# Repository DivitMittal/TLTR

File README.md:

<h1 align='center'>TLTR</h1>
<div align='center'>
    
</div>

---

<div align='center'>

</div>

---

A bespoke cross-platform multi-layer 38-key keyboard layout for programmers, i.e., it optimizes for:

1. Minimal mouse/trackpad dependency
2. Convenient numbers & symbols access
3. Execution of complex keyboard shortcuts w/o cumbersome finger gymnastics.
4. Interoperability b/w [ANSI US](https://commons.wikimedia.org/wiki/File:ANSI_Keyboard_Layout_Diagram_with_Form_Factor.svg) & other ergo-split keyboard configurations, viz., [corne](https://github.com/foostan/crkbd/), [cantor](https://github.com/diepala/cantor), [ferris](https://github.com/pierrechevalier83/ferris), etc..

---

| Layers                                                                                        | Functionality                  |
| --------------------------------------------------------------------------------------------- | ------------------------------ |
| [Colemak Mod-DH(Curl), Wide, Angle](https://github.com/ColemakMods/mod-dh?tab=readme-ov-file) | English                        |
| TL                                                                                            | Navigation & Modifiers keys    |
| TR                                                                                            | Numbers & Symbols              |
| TLTR                                                                                          | Mouse, Media & Display control |

<div align='center'>
    <table>
        <tr>
            <th>Split Keyboard Layout</th>
            <th>ANSI Keyboard Layout</th>
        </tr>
        <tr>
            <td>
                
            </td>
            <td>
                
            </td>
        </tr>
    </table>
</div>

---

## Can be deployed via:

### Software-based (works with any keyboard):

1. [Kanata](https://github.com/jtroo/kanata/) - Cross-platform key remapper
   1. macOS
      - Dependencies:
        1. [Karabiner-DriverKit](https://github.com/pqrs-org/Karabiner-DriverKit-VirtualHIDDevice)
   2. Windows
      - Dependencies:
        1. [InterceptionDriver](https://github.com/oblitum/Interception)
   3. \*nix
      - Dependencies:
        1. `xset` (X11) for the display-off key

### Hardware-based (firmware flashed to keyboard):

2. [QMK Firmware](https://qmk.fm/) - For programmable keyboards
   - Target keyboard: [Piantor](https://github.com/beekeeb/piantor) (RP2040-based Cantor variant)
   - Firmware location: `qmk/piantor_tltr/`
   - Build instructions: See [qmk/README.md](qmk/README.md)

---

## Physical implementation

### Column-staggered ergo-split keyboard, i.e., [Cantor](https://github.com/diepala/cantor)([Piantor](https://github.com/beekeeb/piantor) specifically) with Cherry MX1A Red Switches

---

## Optional: Dual Foot Pedals

Hands-free control via USB or serial foot pedals. Includes both Arduino Uno (serial) and RP2040 (native USB HID) sketches with gesture recognition.

See [pedals/README.md](./pedals/) for setup, keymap, and configuration.

The RP2040 pedal sketch has a matching carrier PCB and 3D-printable enclosure. Both are generated: the board as a KiCad 10 project, the enclosure with build123d. See [hardware/README.md](./hardware/).

---

**Inspired by:** [Seniply](https://github.com/stevep99/seniply)

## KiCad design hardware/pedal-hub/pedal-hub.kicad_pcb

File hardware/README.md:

# Hardware

Electronics (KiCad 10) and 3D-printable enclosures (build123d) for TLTR
accessories. Every KiCad file here is **generated**: edit the generator, then
regenerate. The committed `.kicad_*` files are what you open in KiCad, send to
a fab, or inspect with the Konnect MCP.

| Board | What | Firmware |
| --- | --- | --- |
| [`pedal-hub/`](pedal-hub/) | RP2040-Zero carrier with two 6.35 mm footswitch jacks | [`pedals/rp2040-dual-pedal-hid`](../pedals/rp2040-dual-pedal-hid/) |

## Layout

```
hardware/
  kigen/               generator library: S-expression I/O, schematic writer, pcbnew board builder
  <board>/generate.py  the design: parts, nets, placement, routing, enclosure data
  <board>/*.kicad_*    generated KiCad 10 project (schematic, board, project-local libraries)
  <board>/docs/        schematic PDF/SVG, top/bottom copper renders
  <board>/<board>.step bare-board STEP from KiCad
  <board>/mechanical.json  outline, holes, edge cutouts, heights -> cad/enclosure.py
cad/
  enclosure.py         parametric tray + lid (build123d)
  out/<board>/         tray/lid STEP + STL, fit-check assembly STEP, preview SVG
scripts/
  kicad                run kicad-cli / KiCad's python3: native install, else the kicad/kicad:10.0 container
  hardware             regenerate everything (boards, checks, exports, enclosures)
```

## Regenerate

```sh
scripts/hardware                                   # all boards + enclosures
scripts/kicad python3 hardware/pedal-hub/generate.py --export   # one board
uv run cad/enclosure.py hardware/pedal-hub/mechanical.json      # one enclosure
```

`generate.py` fails unless all of these are clean:

- `kicad-cli sch erc` (all severities)
- `kicad-cli pcb drc --schematic-parity` (all severities, including unconnected items)

Reports go to `.validation/<board>/` (gitignored). The
[`hardware-check`](../.github/workflows/hardware-check.yml) workflow runs the
same generators in the `kicad/kicad:10.0` container and fails if the committed
KiCad files drift from their generators.

**Requirements:** a native KiCad 10, or Docker for the container fallback. On
macOS nixpkgs marks KiCad broken, so install KiCad.app or run a Docker VM, such
as `colima start`. Enclosures need [uv](https://docs.astral.sh/uv/). It
installs `build123d` from the script's inline metadata.

## Why generated KiCad, not atopile

atopile 0.15 announces itself as the last CLI release. Its successor is a
hosted app that needs `ato auth login`. Plain KiCad files plus a small
deterministic generator keep the design reviewable in git, buildable offline
and in CI, and openable in the KiCad GUI and in [Konnect](https://github.com/mixelpixx/Konnect)
for hand edits. If you hand-edit a board in KiCad, port the change back into
`generate.py`, or stop regenerating that board.

## Pedal hub

- **U1** Waveshare RP2040-Zero on pin headers. Only the two side rows are used
  (rows 15.24 mm apart, 2.54 mm pitch). USB-C is flush with the back edge.
- **J1/J2** Neutrik NMJ6HCD2 6.35 mm (¼″) stereo jacks. Tip goes to the GPIO.
  Ring and sleeve go to GND, so TS footswitches and tip-to-ring TRS pedals both
  work.
- **R1/R2 330 Ω + C1/C2 100 nF** series RC on each input. It limits ESD/RF
  pickup on long pedal cables. τ = 33 µs, invisible to the 25 ms firmware
  debounce.
- 2-layer, all through-hole. Signals are on B.Cu; F.Cu is an unbroken ground
  plane. Four M3 holes are 4 mm from the corners.

**BOM:** 1× RP2040-Zero, 2× 1×9 2.54 mm male headers, 2× NMJ6HCD2, 2× 330 Ω
¼ W, 2× 100 nF disc ceramic. Enclosure: 4× M3×20 cap screws, 4× M3 heat-set
inserts (4.0 mm hole), and optionally 4× 10 mm rubber feet.

### Verify before you order

Not all of these come from measurements:

| Item | Source | Status |
| --- | --- | --- |
| RP2040-Zero row spacing 15.24 mm, pin order | community footprint (CountParadox/RP2040-Zero-Kicad) cross-checked with Waveshare pinout | verify with calipers |
| NMJ6HCD2 mouth on the footprint's +X side | stock KiCad footprint, ferrule outline | check datasheet |
| Jack axis 6.6 mm and USB-C centre 5.1 mm above the PCB | datasheet-style estimates | measure the parts; edit `cutouts` in `generate.py` |
| Pedals use 6.35 mm plugs | assumption | for 3.5 mm pedals swap `JACK_FP` (e.g. `Jack_3.5mm_CUI_SJ1-3523N_Horizontal`) and re-route |

The enclosure prints without supports: the tray stands upright and the lid
prints top-down. The back-wall holes are bridged circles.

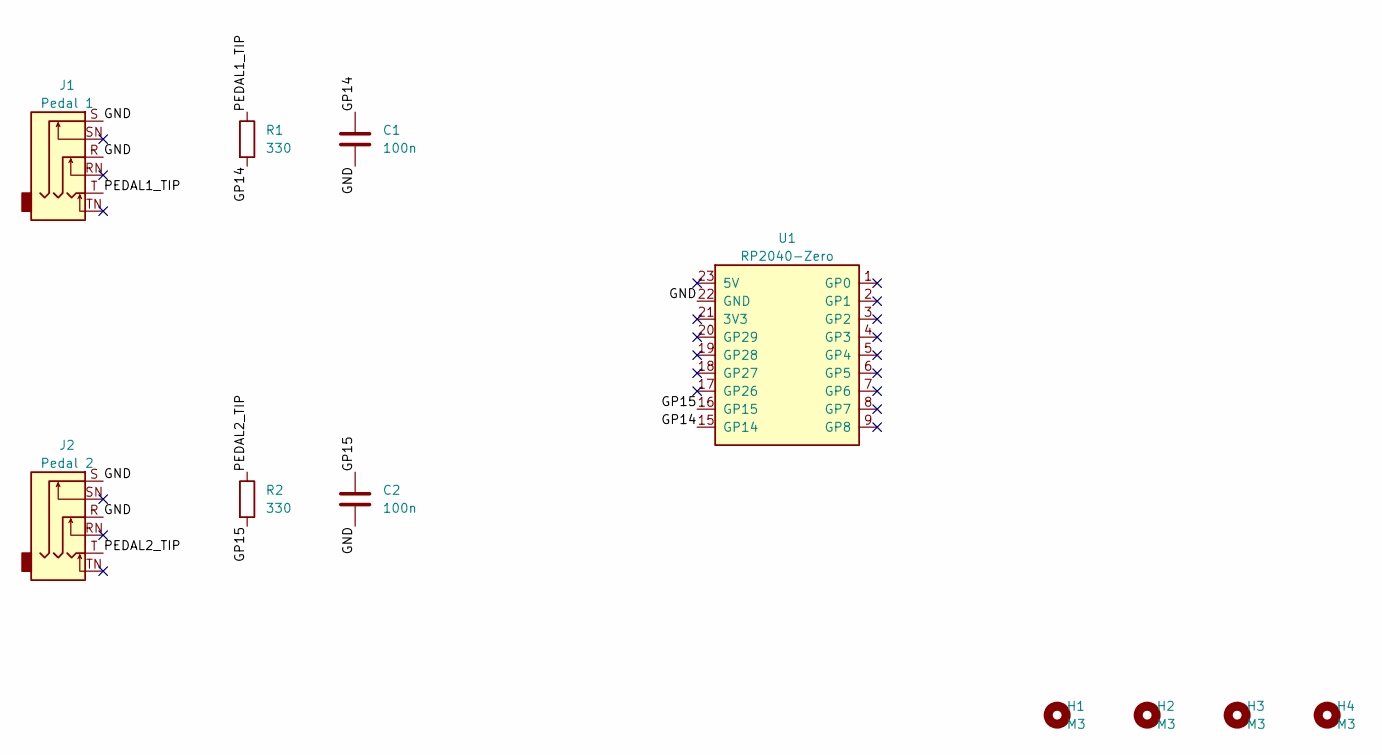
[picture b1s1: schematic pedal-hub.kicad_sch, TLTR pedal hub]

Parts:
C1, C2: 100n; C_Disc_D3.0mm_W1.6mm_P2.50mm
H1, H2, H3, H4: M3; MountingHole_3.2mm_M3
J1: Pedal 1; Jack_6.35mm_Neutrik_NMJ6HCD2_Horizontal; MPN Neutrik NMJ6HCD2
J2: Pedal 2; Jack_6.35mm_Neutrik_NMJ6HCD2_Horizontal; MPN Neutrik NMJ6HCD2
R1, R2: 330; R_Axial_DIN0207_L6.3mm_D2.5mm_P7.62mm_Horizontal
U1: RP2040-Zero; RP2040-Zero_TH; MPN Waveshare RP2040-Zero (SKU 20187)

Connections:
/GND: C1.2, C2.2, J1.R, J1.S, J2.R, J2.S, U1.22 (GND)
/GP14: C1.1, R1.2, U1.15 (GP14)
/GP15: C2.1, R2.2, U1.16 (GP15)
/PEDAL1_TIP: J1.T, R1.1
/PEDAL2_TIP: J2.T, R2.1

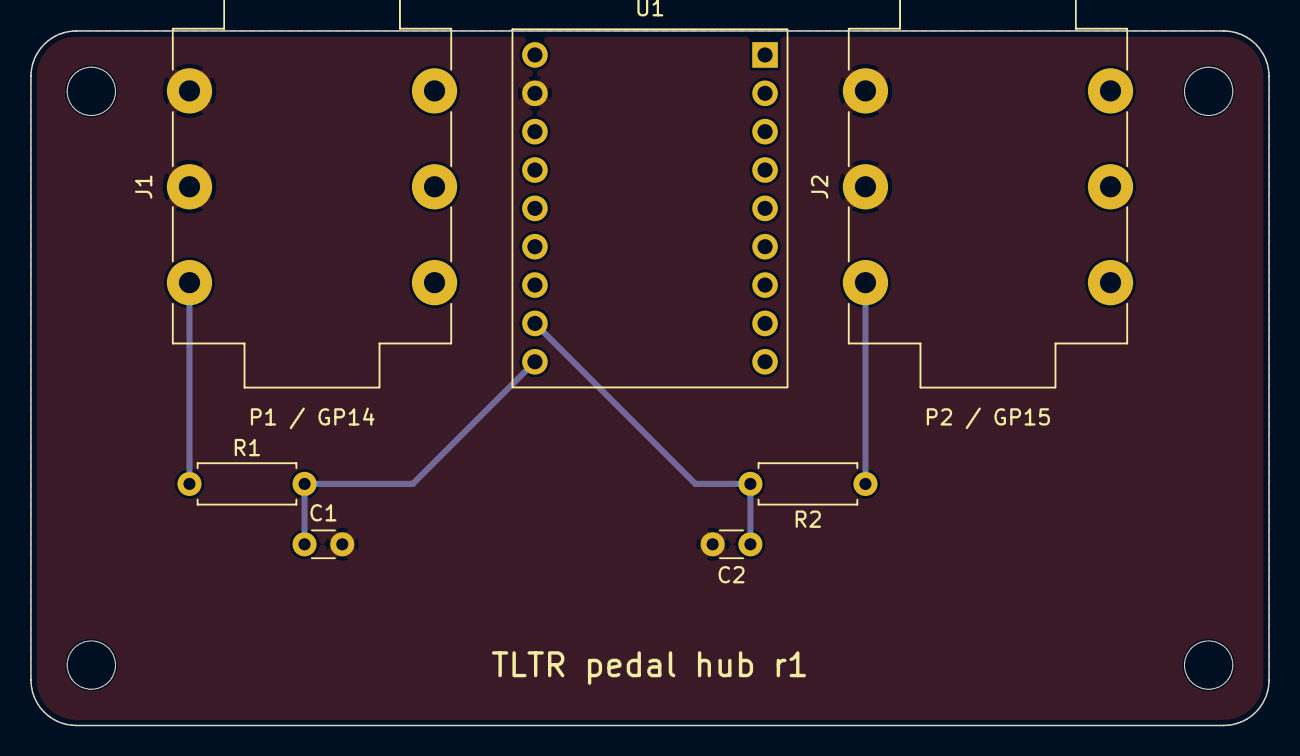
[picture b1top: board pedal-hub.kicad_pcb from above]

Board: 2 copper layers, 82.0 x 46.0 mm, 11 parts (0 on the bottom side), 5 nets.

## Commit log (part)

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2024-09-19 Windows: added & tested brightness & sleep functionality
2024-09-21 Major documentation update
2024-09-21 Updated: README
2024-09-23 fix: Major fixes
2024-10-06 Added: editorconfig
2024-12-01 Reformating: karabiner json 4spaces -> 2spaces
2025-03-09 Fix: README path for logo
2025-03-31 fix: minor changes to scroll & mouse speed
2025-04-18 feat: added nix support with flakes & development ephemeral environment with treefmt
2025-05-10 cleanup: misc
2025-06-09 fix: switching to default reverted back to TLTR+sp due to collision with other TLTR layer shortcuts
2025-06-09 docs(add): physical keyboard implementation images & update README.md
2025-06-09 feat: add flake-parts modules, viz., actions-nix, git-hooks, treefmt-nix
2025-06-09 refactor: keymap-drawer svg output into assets
2025-06-10 docs: reformat README.md
2025-06-10 fix(macOS): migrate from vk_consumer_keys to Apple Shortcuts via osascripts for media keys
2025-06-10 docs(keymap-drawer): add the TLTR combo & function keys
2025-06-16 docs: update docs for split keyboard
2025-06-19 regress: remove QWERTY layer
2025-06-19 ci: incorporate DeterminateSystems Magic Nix Cache & thus, GitHub Actions Cache
2025-06-19 ci: add keymap-drawer svg generation using the uv github action setup with caching
2025-06-19 chore: update keymap-drawer config in accordance with the updated tltr layout
2025-06-19 ci: fix workflow's ability to push to repo
2025-06-19 fix(keymap-drawer): configuration in accordance with the latest layout
2025-06-21 fix(kanata): tap-hold timeout
2025-06-23 fix(git): nix build output, i.e., result ignore filter
2025-06-26 feat(kanata): change left thumb key to standard shift
    Replaces the sticky shift key on the left thumb with a
    standard shift key.
2025-06-28 feat(nix): major update to nix flake configuration
    Updates .gitignore, flake.lock, actions.nix, checks.nix, and
    devshells.nix to improve development environment and tooling.
2025-07-07 docs: adjust logo size in README
    Ensures logo displays correctly by setting both height and width.
2025-07-23 refactor(nix): replace pre-commit-hooks with git-hooks
    Migrates from `pre-commit-hooks` to `git-hooks` for managing
    git hooks. This change updates flake.nix and checks.nix to
    reflect the new dependency.
2025-07-28 fix(ci): use nix-installer-action in flake-lock-update
2025-07-29 flake.lock: Update
    Flake lock file updates:
    • Updated input 'OS-nixCfg':
    'github:DivitMittal/OS-nixCfg/d2bae5c201bdc33ff9829853a12ce05f32e23c50?narHash=sha256-WrB4kz2276uzqu0EgZWQCV49r0HUd8LW9Kr3COQ9RL8%3D' (2025-07-28)
    → 'github:DivitMittal/OS-nixCfg/98c363cf4234084911d8df47250e24999abb0627?narHash=sha256-LZYgluLWnvVsxg1bEq5xTc69oRolCGb3uT/6jzbIB14%3D' (2025-07-29)
    • Updated input 'nixpkgs':
    'github:nixos/nixpkgs/648f70160c03151bc2121d179291337ad6bc564b?narHash=sha256-FK8iq76wlacriq3u0kFCehsRYTAqjA9nfprpiSWRWIc%3D' (2025-07-28)
2025-07-30 refactor(flake): simplify flake configuration via hermetic uv integration
2025-08-05 chore(ci): update nix-installer-action to v19
2025-08-10 flake.lock: Update
    Flake lock file updates:
    • Updated input 'OS-nixCfg':
    'github:DivitMittal/OS-nixCfg/df1126b41f5552d59d9695252013507c3482441a?narHash=sha256-I/dCKTIxwEuQ1UmwWnST32TeOGOUHpqJqtH5E5ElnLU%3D' (2025-08-05)
    → 'github:DivitMittal/OS-nixCfg/68e288135721bf104ca092f407d55b3176e7bb85?narHash=sha256-3yK001k54b1bVkIuC3YkuogV14DLCFHmIeclE5xdjpc%3D' (2025-08-08)
    • Updated input 'flake-parts':
    'github:hercules-ci/flake-parts/67df8c627c2c39c41dbec76a1f201929929ab0bd?narHash=sha256-XKqDMN1/Qj1DKivQvscI4vmHfDfvYR2pfuFOJiCeewM%3D' (2025-08-01)
2025-08-17 fix(kanata): update scroll move settings
2025-08-31 flake.lock: Update
    Flake lock file updates:
    • Updated input 'OS-nixCfg':
    'github:DivitMittal/OS-nixCfg/181346e44983840eff697380ece8a181a25979b9?narHash=sha256-u3iZ6FyO%2BTQZWGk2cjnOILcT5TnQ0FbOCUQK7YOPOoo%3D' (2025-08-17)
    → 'github:DivitMittal/OS-nixCfg/b86152e112e8353b6db4c4339225352bffde13d9?narHash=sha256-Mbc2W2z34sPM9mgWrTYIO60qFm11jBrBh%2B/8qeHGdmc%3D' (2025-08-30)
    • Updated input 'nixpkgs':
    'github:nixos/nixpkgs/f937f8ecd1c70efd7e9f90ba13dfb400cf559de4?narHash=sha256-4/Jd%2BLkQ2ssw8luQVkqVs9spDBVE6h/u/hC/tzngsPo%3D' (2025-08-22)
2025-09-06 feat(formatters): add C code formatting
2025-09-13 chore(ai): update claude settings and gitignore
2025-09-28 flake.lock: Update
    Flake lock file updates:
    • Updated input 'nixpkgs':
    'github:nixos/nixpkgs/d3d7744936d05dcdce1e6f5c20733a400614afbf?narHash=sha256-/aQISPwiXEZ6P620114G7wX1fSFO26Nlt3VGqc7dF0s%3D' (2025-09-19)
    → 'github:nixos/nixpkgs/bd1e762364c6d657a67a05b44a6c04646947e739?narHash=sha256-LBewTiqEEIslXle4BrkAUlEG7uGvN9mS6G7hY0l04w4%3D' (2025-09-27)
    • Updated input 'treefmt-nix':
    'github:numtide/treefmt-nix/128222dc911b8e2e18939537bed1762b7f3a04aa?narHash=sha256-/DbPkh6PZOgfueCbs3uzlk4ASU2nPPsiVWhpMCNkAd0%3D' (2025-09-18)
2025-10-14 docs: remove redundant text from CLAUDE.md
2025-10-28 chore(flake): specify pre-commit package
    Refactor `perSystem` to allow access to `pkgs`.
    Explicitly configure `prek` as the pre-commit package and `gitFull` for git operations.
2025-10-29 feat(qmk): inital implementation for qmk
    This commit introduces a comprehensive set of features and configurations to align the TLTR QMK keymap with its Kanata counterpart.
    Key changes include:
    - **Advanced Layer Management:** Implemented complex thumb-based layer switching for `_TL`, `_TR`, and `_TLTR` layers, including combined activation logic.
    - **Caps Word:** Added `caps_word_press_user` for intelligent Caps Word behavior, matching Kanata's continuation rules.
    - **One-shot Modifiers:** Introduced custom one-shot modifiers for `sWin` (Alt+Ctrl+Meta), `sHyp` (Alt+Ctrl+Shift+Meta), and `sFn` (function modifier).
    - **Multi-mode Mouse Control:** Developed a flexible mouse system with slow,
2025-12-17 ci(workflows): regenerate workflow files
    Workflow files were regenerated using actions.nix, adding a header to indicate their autogenerated status.
    The nix-installer-action was updated from v19 to v21 in flake-check.yml and flake-lock-update.yml as part of this regeneration.
2025-12-17 chore(mcp): update context name
2025-12-17 feat(qmk): enhance piantor_tltr keymap with key repeat, modifiers, and unicode
    Major improvements to QMK firmware implementation:
    Features added:
    - Enable Caps Word and Unicode support
    - Add Unicode mode cycling (KC_UMODE) for cross-platform ₹ symbol
    - Replace underscore with Enter key on right home row
    Key repeat fixes:
2025-12-18 feat(qmk): reverse mouse scroll directions for natural scrolling
    Implement natural/inverted scrolling behavior in scroll mode:
    Previous behavior (traditional):
    - M↑ → Scroll up | M↓ → Scroll down
    - M← → Scroll left | M→ → Scroll right
    New behavior (natural):
    - M↑ → Scroll down (content moves down, like pushing page up)
2025-12-18 fix(qmk): fix compilation errors and make shift key non-sticky
    Compilation fixes:
    - Move MOUSEKEY_* macros from keymap.c to config.h to avoid redefinition errors
    - Add forward declarations for get_mouse_speed() and get_wheel_speed()
    - Move mouse state variables before matrix_scan_user() to fix undeclared errors
    - Add empty key_overrides array to satisfy QMK introspection
    - Remove duplicate mouse variable declarations
2025-12-18 fix(qmk): make scrolling speed respond to precise/slow mouse keys
    The mouse wheel speed constants were all set to 1, which meant
    scrolling speed never changed regardless of whether precise or slow
    mouse keys were active. Updated the constants to provide proper speed
    differentiation:
    - MOUSE_WHEEL_PRECISE: 1 (very slow)
    - MOUSE_WHEEL_SLOW: 2 (slow)
2025-12-18 feat(qmk): increase default mouse movement speed
    Increased default mouse cursor and scroll speeds for faster navigation:
    - MOUSE_MOVE_DEFAULT: 8 → 12 (50% faster cursor movement)
    - MOUSE_WHEEL_DEFAULT: 3 → 4 (33% faster scrolling)
    Precise and slow modes remain unchanged for fine control when needed.
2025-12-18 docs(qmk): use qmk setup instead of manual git clone
    Replace manual git clone workflow with 'qmk setup' which handles
    repository cloning and initial configuration automatically. Also
    clarify that qmk compile can be run from any directory.
2025-12-18 docs(qmk): clean up and correct README documentation
    - Update keyboard description to "Modified Piantor"
    - Correct layout specification from 42-key to 38-key split
    - Remove redundant documentation sections from piantor_tltr README
    - Simplify configuration overview
2025-12-18 feat(qmk): implement variable-speed mouse control with smooth cursor movement
    - Add separate intervals for cursor movement (8-16ms) vs scrolling (32-100ms)
    - Increase cursor movement speeds for smoother tracking (4-16 pixels/report)
    - Implement dynamic interval selection based on scroll mode
    - Keep scrolling slow and controlled while maintaining smooth cursor movement
    - Default cursor: 125Hz update rate for very smooth movement
    - Precise scroll: 10Hz update rate for surgical precision
2025-12-18 fix(qmk): COLEMAK, TL, TR and TLTR ASCII diagrams
    Complete ASCII diagram fix
    - Fixed all corrupted ASCII diagrams in QMK keymap
    - COLEMAK layer: Proper 38-key layout visualization
    - TL layer: Clean navigation and modifier layout
    - TR layer: Completely rebuilt from corrupted state
    - TLTR layer: Mouse, media and system controls
2025-12-19 fix(keymap): correct path to ansi-keyboard.json for CI
    The path must be relative to the repository root since the GitHub
    Actions workflow runs keymap-drawer from the repo root directory.
2025-12-20 feat(qmk): implement tap-hold boot/reboot keycode, remove ASCII Diagrams & kanata references
    - Add KC_BOOT_HOLD custom keycode with tap-hold behavior
    - Tap (<200ms): Reboot keyboard using RP2040 watchdog_reboot()
    - Hold (≥200ms): Enter bootloader mode for firmware flashing
    - Map to TL+TR+; key position in TLTR layer
    - Add hardware/watchdog.h include for RP2040 reboot function
    - Reorganize EXTRAKEY_ENABLE in rules.mk for clarity
2025-12-20 fix(qmk): implement proper one-shot behavior for Fn modifier
    Previously, the Fn modifier (KC_OS_FN) would deactivate immediately upon
    release, preventing cross-layer one-shot usage (e.g., tap Fn in TL layer,
    then press TR to access function keys). This made Fn inconsistent with
    other one-shot modifiers like KC_OS_WIN and KC_OS_HYP.
    Changes:
    - Add fn_oneshot_active flag and os_fn_used/os_fn_timer tracking
2025-12-22 refactor(ai): Move .mcp.json to .claude/ directory and create CLAUDE.md symlink
2026-01-15 refactor(qmk): remove comment patterns
    Strip decorative section banners, obvious inline comments, and
    redundant descriptions while preserving technical annotations.
2026-03-05 chore: update config files
    - Fix .gitignore serena directory pattern
    - Remove empty env object from .mcp.json
2026-05-27 feat(kanata): add mouse buttons 3, 4, and 5 to TLTR layer
    Place middle click (🖰3) above and back/forward (🖰4/🖰5) below the
    existing click buttons, keeping all five on the left hand in TLTR.
2026-06-04 feat(karabiner): add scroll direction toggle for natural scrolling compatibility
    Mirror qmk commit 746266b. New TLTR_scroll_reversed variable, toggled
    by slash key on TLTR layer. Existing scroll keys (l/o/k/;) gated on
    =0; mirrored manipulators with inverted wheel values fire when =1.
2026-06-08 ci(actions): remove scheduled run from flake-lock-update workflow
